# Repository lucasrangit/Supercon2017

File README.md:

# Supercon2017
Source Files for Supercon 2017

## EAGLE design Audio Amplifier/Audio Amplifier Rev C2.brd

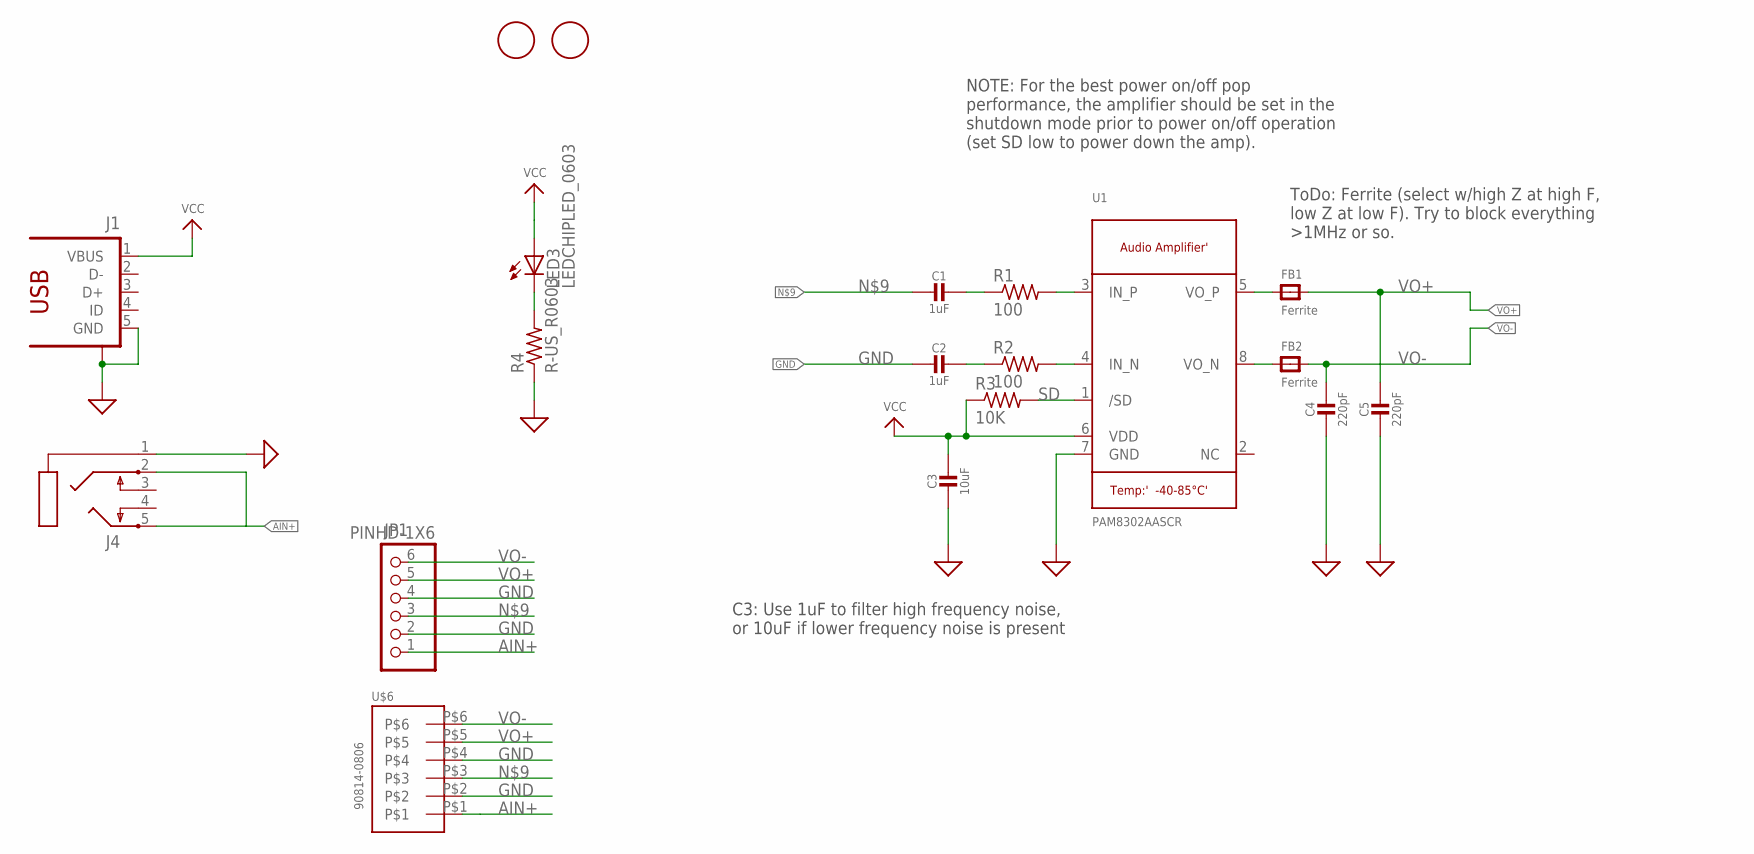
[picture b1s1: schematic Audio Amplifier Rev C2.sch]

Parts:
C1, C2: 1uF; 0805-NO
C3: 10uF; 0805-NO
C4, C5: 220pF; 0805-NO
FB1, FB2: Ferrite; _0805
J1: 1981584-1
J4: STEREOJACK; STX3100
JP1: PINHD-1X6; 1X06
LED3: LEDCHIPLED_0603; CHIPLED_0603
R1, R2: 100; R0603
R3: 10K; R0603
R4: R-US_R0603; R0603
U1: PAM8302AASCR; MSOP8_0.65MM
U$3, U$4: FIDUCIAL; FIDUCIAL_1MM
U$6: 90814-0806

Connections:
AIN+: J4.2, J4.5, JP1.1, U$6.P$1
GND: C2.2, C3.2, C4.2, C5.2, J1.5 (GND), J1.S1, J4.1, JP1.2, JP1.4, R4.1, U1.7 (GND), U$6.P$2, U$6.P$4
unnamed: R2.2, U1.4 (IN_N)
unnamed: LED3.C, R4.2
unnamed: R1.2, U1.3 (IN_P)
unnamed: C2.1, R2.1
unnamed: FB2.1, U1.8 (VO_N)
unnamed: FB1.1, U1.5 (VO_P)
unnamed: C1.1, R1.1
unnamed: C1.2, JP1.3, U$6.P$3
SD: R3.2, U1.1 (/SD)
VCC: C3.1, J1.1 (VBUS), LED3.A, R3.1, U1.6 (VDD)
VO+: C5.1, FB1.2, JP1.5, U$6.P$5
VO-: C4.1, FB2.2, JP1.6, U$6.P$6

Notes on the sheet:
ToDo: Ferrite (select w/high Z at high F, low Z at low F). Try to block everything >1MHz or so.
C3: Use 1uF to filter high frequency noise, or 10uF if lower frequency noise is present
NOTE: For the best power on/off pop performance, the amplifier should be set in the shutdown mode prior to power on/off operation (set SD low to power down the amp).

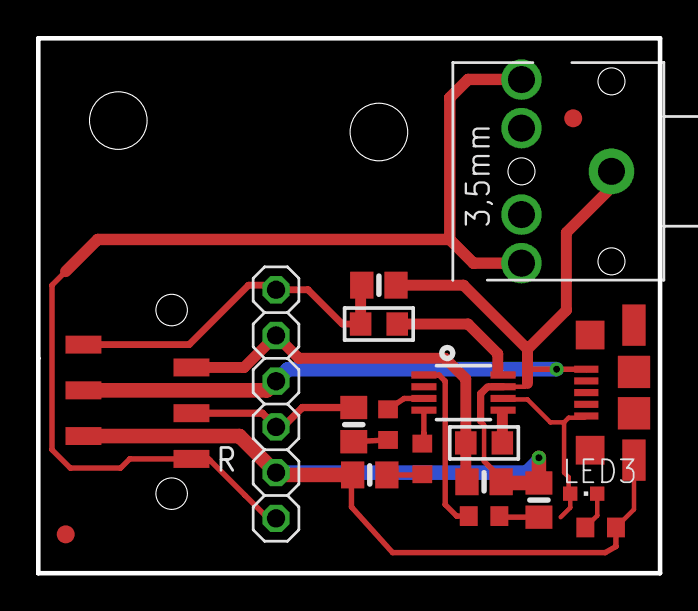
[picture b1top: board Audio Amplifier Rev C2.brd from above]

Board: 2 copper layers, 34.5 x 29.7 mm, 19 parts (0 on the bottom side), 14 nets.

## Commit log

2017-11-11 Initial Commit - Source Files and Libraries
2017-11-11 start of workshop
2017-11-11 remove mac and zip file
2017-11-11 rename folder
2017-11-11 remove backup files
